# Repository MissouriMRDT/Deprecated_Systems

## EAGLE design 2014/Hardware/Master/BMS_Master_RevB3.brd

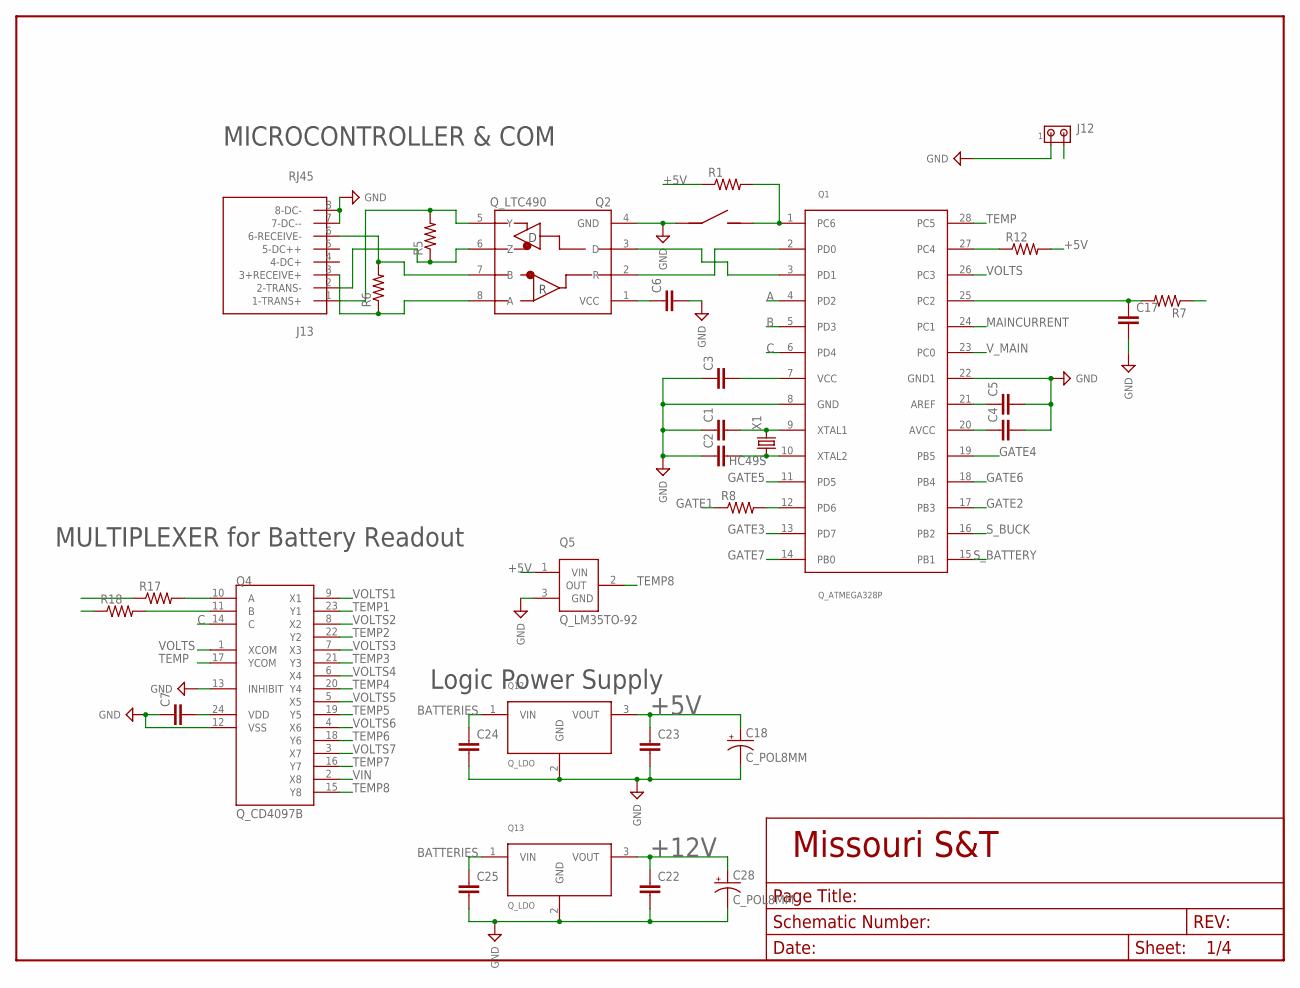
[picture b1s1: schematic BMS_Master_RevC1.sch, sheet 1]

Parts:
C1, C2, C3, C4, C5, C6, C7, C17, C22, C23, C24, C25: C_CAP_1206; C_1206
C18, C28: C_POL8MM; C_8MM
J1: J_MC32857; J_TOGGLE
J12: J_MTA2P_100; J_MTA100_2P
J13: RJ45; RJ45-CAT5E
Q1: Q_ATMEGA328P; DIP28
Q2: Q_LTC490; DIP8
Q4: Q_CD4097B; WDIP24
Q5: Q_LM35TO-92; TO-92-3
Q12, Q13: Q_LDO; TO-220
R1, R5, R6: R_RES_1206; R_1206
R7, R8, R17, R18: R_1/4W
R12: R_RES_0805; R_0805
X1: HC49S; HC-49

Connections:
+5V: C3.2, C4.1, C6.1, C7.2, C18.+, C23.1, Q1.7 (VCC), Q1.20 (AVCC), Q2.1 (VCC), Q4.24 (VDD), Q5.1 (VIN), Q12.3 (VOUT), R1.1, R12.2; also elsewhere on the board
+12V: C22.1, C28.+, Q13.3 (VOUT); also elsewhere on the board
A: Q1.4 (PD2), R17.1
B: Q1.5 (PD3), R18.1
BATTERIES: C24.1, C25.1, Q12.1 (VIN), Q13.1 (VIN); also elsewhere on the board
C: Q1.6 (PD4), Q4.14 (C)
CURRENT: R7.1; also elsewhere on the board
GATE1: R8.1; also elsewhere on the board
GATE2: Q1.17 (PB3); also elsewhere on the board
GATE3: Q1.13 (PD7); also elsewhere on the board
GATE4: Q1.19 (PB5); also elsewhere on the board
GATE5: Q1.11 (PD5); also elsewhere on the board
GATE6: Q1.18 (PB4); also elsewhere on the board
GATE7: Q1.14 (PB0); also elsewhere on the board
GND: C1.1, C2.1, C3.1, C4.2, C5.2, C6.2, C7.1, C17.2, C18.-, C22.2, C23.2, C24.2, C25.2, C28.-, J1.P$1 (1), J12.1, J13.7 (7-DC--), J13.8 (8-DC-), Q1.8 (GND), Q1.22 (GND1), Q2.4 (GND), Q4.12 (VSS), Q4.13 (INHIBIT), Q5.3 (GND), Q12.2 (GND), Q13.2 (GND); also elsewhere on the board
MAINCURRENT: Q1.24 (PC1); also elsewhere on the board
unnamed: C2.2, Q1.10 (XTAL2), X1.P$1 (1)
unnamed: C1.2, Q1.9 (XTAL1), X1.P$2 (2)
unnamed: Q4.10 (A), R17.2
unnamed: C5.1, Q1.21 (AREF)
unnamed: Q4.11 (B), R18.2
unnamed: J1.P$2 (2), Q1.1 (PC6), R1.2
unnamed: C17.1, Q1.25 (PC2), R7.2
unnamed: Q1.12 (PD6), R8.2
unnamed: Q1.2 (PD0), Q2.2 (R)
unnamed: Q1.3 (PD1), Q2.3 (D)
unnamed: J13.1 (1-TRANS+), Q2.5 (Y), R5.2
unnamed: J13.2 (2-TRANS-), Q2.6 (Z), R5.1
unnamed: J13.6 (6-RECEIVE-), Q2.7 (B), R6.2
unnamed: J13.3 (3+RECEIVE+), Q2.8 (A), R6.1
PANIC: J12.2, Q1.27 (PC4), R12.1
S_BATTERY: Q1.15 (PB1); also elsewhere on the board
S_BUCK: Q1.16 (PB2); also elsewhere on the board
TEMP: Q1.28 (PC5), Q4.17 (YCOM)
TEMP1: Q4.23 (Y1); also elsewhere on the board
TEMP2: Q4.22 (Y2); also elsewhere on the board
TEMP3: Q4.21 (Y3); also elsewhere on the board
TEMP4: Q4.20 (Y4); also elsewhere on the board
TEMP5: Q4.19 (Y5); also elsewhere on the board
TEMP6: Q4.18 (Y6); also elsewhere on the board
TEMP7: Q4.16 (Y7); also elsewhere on the board
TEMP8: Q4.15 (Y8), Q5.2 (OUT)
VIN: Q4.2 (X8); also elsewhere on the board
VOLTS: Q1.26 (PC3), Q4.1 (XCOM)
VOLTS1: Q4.9 (X1); also elsewhere on the board
VOLTS2: Q4.8 (X2); also elsewhere on the board
VOLTS3: Q4.7 (X3); also elsewhere on the board
VOLTS4: Q4.6 (X4); also elsewhere on the board
VOLTS5: Q4.5 (X5); also elsewhere on the board
VOLTS6: Q4.4 (X6); also elsewhere on the board
VOLTS7: Q4.3 (X7); also elsewhere on the board
V_MAIN: Q1.23 (PC0); also elsewhere on the board

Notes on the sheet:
MICROCONTROLLER & COM
MULTIPLEXER for Battery Readout
Logic Power Supply

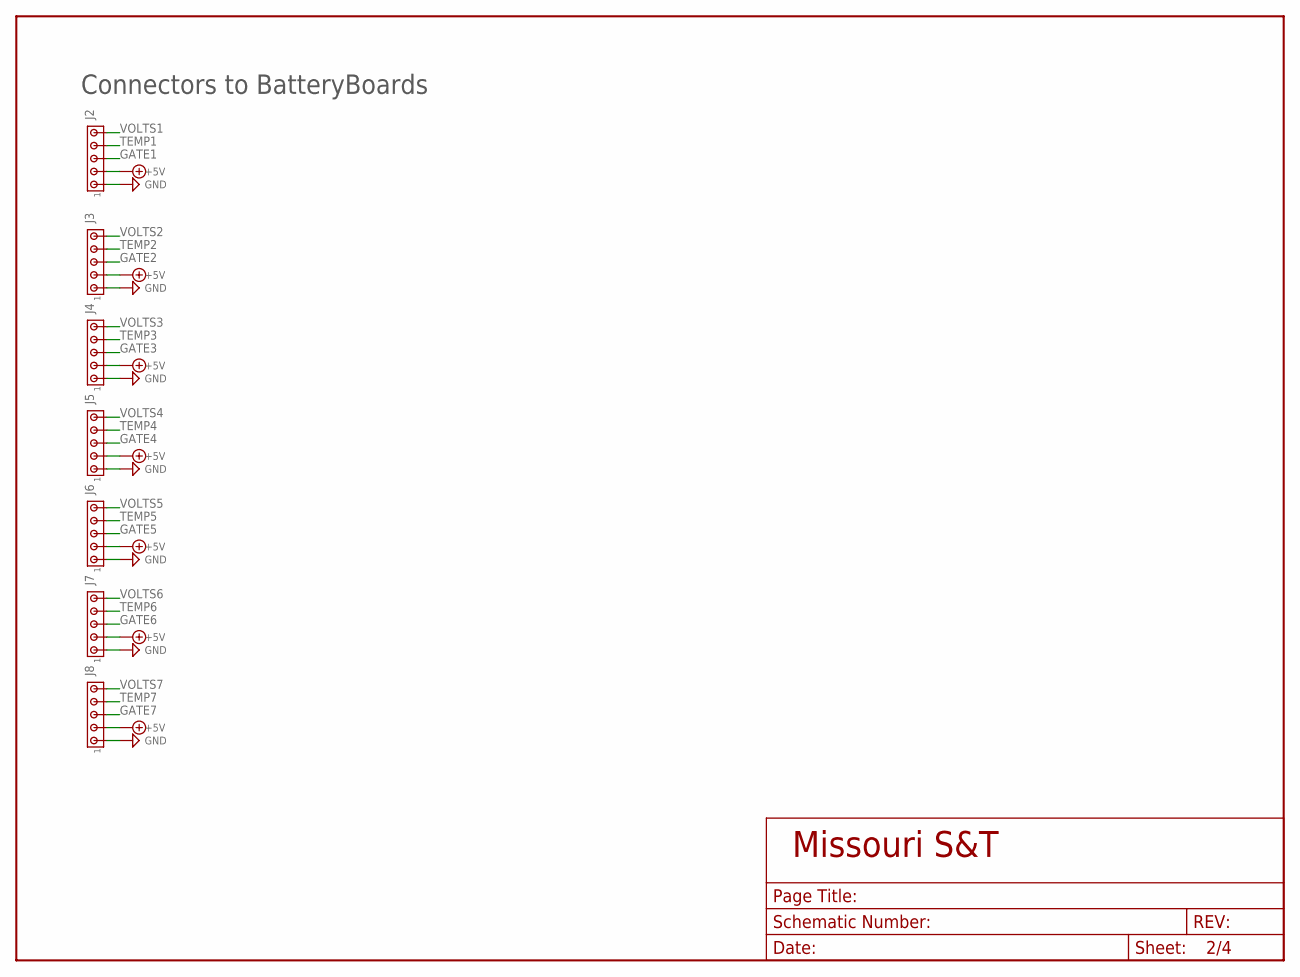
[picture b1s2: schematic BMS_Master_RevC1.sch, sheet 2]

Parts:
J2, J3, J4, J5, J6, J7, J8: J_MTA5P_100; J_MTA100_5P

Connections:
+5V: J2.2, J3.2, J4.2, J5.2, J6.2, J7.2, J8.2; also elsewhere on the board
GATE1: J2.3; also elsewhere on the board
GATE2: J3.3; also elsewhere on the board
GATE3: J4.3; also elsewhere on the board
GATE4: J5.3; also elsewhere on the board
GATE5: J6.3; also elsewhere on the board
GATE6: J7.3; also elsewhere on the board
GATE7: J8.3; also elsewhere on the board
GND: J2.1, J3.1, J4.1, J5.1, J6.1, J7.1, J8.1; also elsewhere on the board
TEMP1: J2.4; also elsewhere on the board
TEMP2: J3.4; also elsewhere on the board
TEMP3: J4.4; also elsewhere on the board
TEMP4: J5.4; also elsewhere on the board
TEMP5: J6.4; also elsewhere on the board
TEMP6: J7.4; also elsewhere on the board
TEMP7: J8.4; also elsewhere on the board
VOLTS1: J2.5; also elsewhere on the board
VOLTS2: J3.5; also elsewhere on the board
VOLTS3: J4.5; also elsewhere on the board
VOLTS4: J5.5; also elsewhere on the board
VOLTS5: J6.5; also elsewhere on the board
VOLTS6: J7.5; also elsewhere on the board
VOLTS7: J8.5; also elsewhere on the board

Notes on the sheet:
Connectors to BatteryBoards

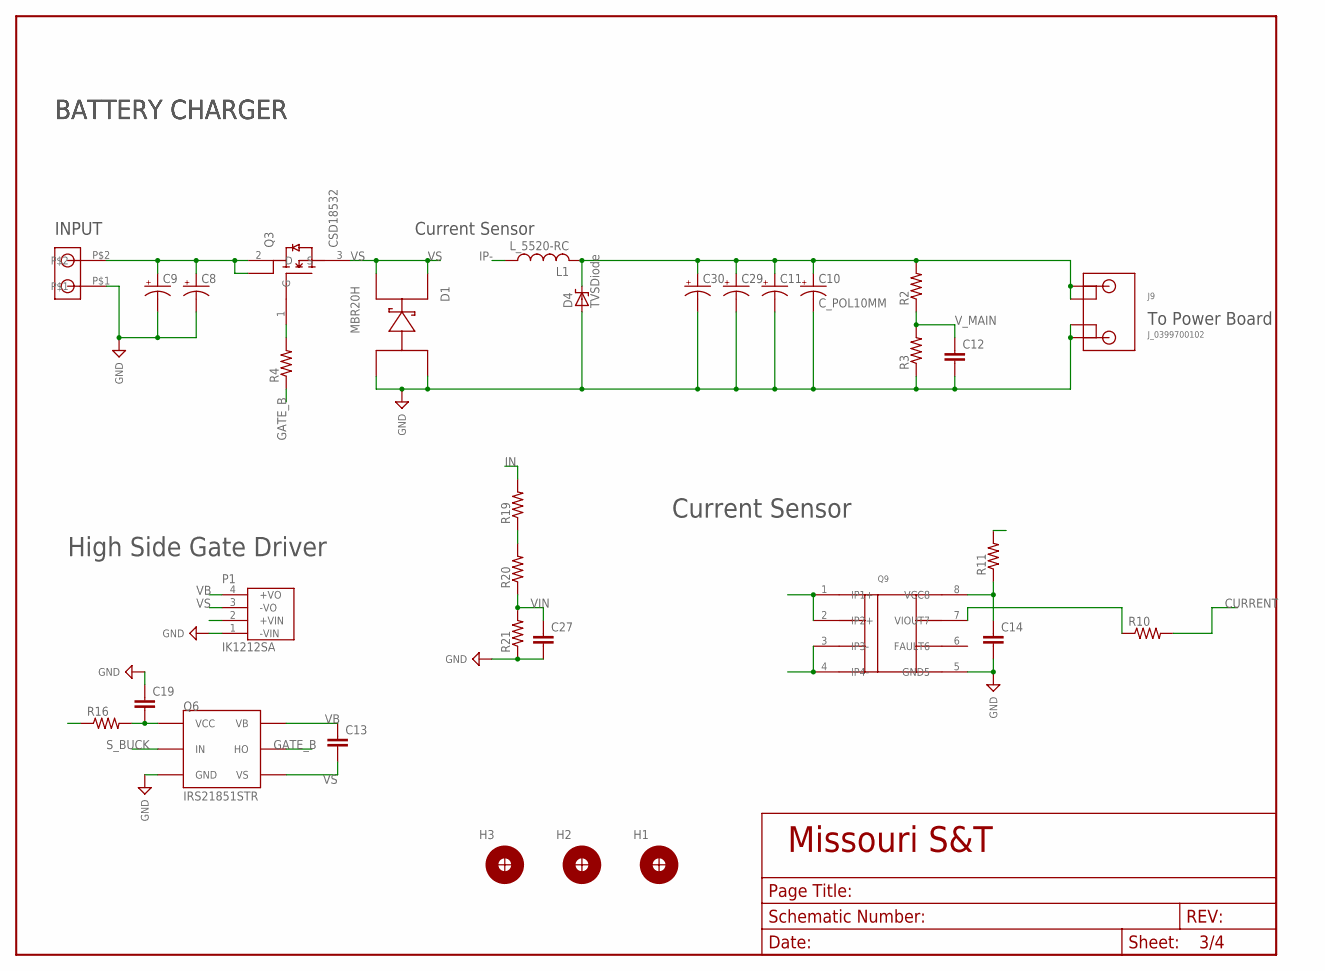
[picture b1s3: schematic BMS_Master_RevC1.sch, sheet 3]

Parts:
C8, C9, C10, C11, C29, C30: C_POL10MM; C_10MM
C12, C13, C14, C19, C27: C_CAP_1206; C_1206
D1: MBR20H; TO-220-FLAT
D4: TVSDiode; DIODE_D3.5MM_LS15.24MM
H1, H2, H3: H_MNTHOLE_#6
J9: J_0399700102; J_2CONHC
J10: J_1546074-2; THERM_BLOCK_2
L1: L_5520-RC
P1: IK1212SA; TME1215S
Q3: CSD18532; TO-220-FLAT
Q6: IRS21851STR; SOIC8
Q9: Q_SO8ACS711; Q_SO8
R2, R10, R11, R16, R19, R20: R_1/4W
R3, R4, R21: R_RES_1206; R_1206

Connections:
+5V: R11.2; also elsewhere on the board
+5V1: C14.1, Q9.8 (VCC8), R11.1; also elsewhere on the board
+12V: R16.1; also elsewhere on the board
+12V1: C19.2, P1.2 (+VIN), Q6.1 (VCC), R16.2
CURRENT: R10.2; also elsewhere on the board
GATE_B: Q6.7 (HO), R4.1
GND: C8.P$2 (-), C9.P$2 (-), C10.P$2 (-), C11.P$2 (-), C12.2, C14.2, C19.1, C27.2, C29.P$2 (-), C30.P$2 (-), D1.1 (A1), D1.3 (A2), D4.A, J9.PIN2-1 (2-1), J9.PIN2-2 (2-2), J10.P$1, P1.1 (-VIN), Q6.4 (GND), Q9.5 (GND5), R3.1, R21.1; also elsewhere on the board
IN: C8.P$1 (+), C9.P$1 (+), J10.P$2, Q3.2 (D), Q3.4, R19.2
IP-: L1.1, Q9.1 (IP1+), Q9.2 (IP2+)
MAIN: C10.P$1 (+), C11.P$1 (+), C29.P$1 (+), C30.P$1 (+), D4.C (K), J9.PIN1-1 (1-1), J9.PIN1-2 (1-2), L1.2, R2.2; also elsewhere on the board
unnamed: Q9.7 (VIOUT7), R10.1
unnamed: R19.1, R20.2
unnamed: Q3.1 (G), R4.2
S_BUCK: Q6.2 (IN); also elsewhere on the board
VB: C13.1, P1.4 (+VO), Q6.8 (VB)
VIN: C27.1, R20.1, R21.2; also elsewhere on the board
VS: C13.2, D1.2 (C1), D1.4 (C2), P1.3 (-VO), Q3.3 (S), Q6.6 (VS), Q9.3 (IP3-), Q9.4 (IP4-)
V_MAIN: C12.1, R2.1, R3.2; also elsewhere on the board

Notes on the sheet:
BATTERY CHARGER
INPUT
Current Sensor
High Side Gate Driver
To Power Board

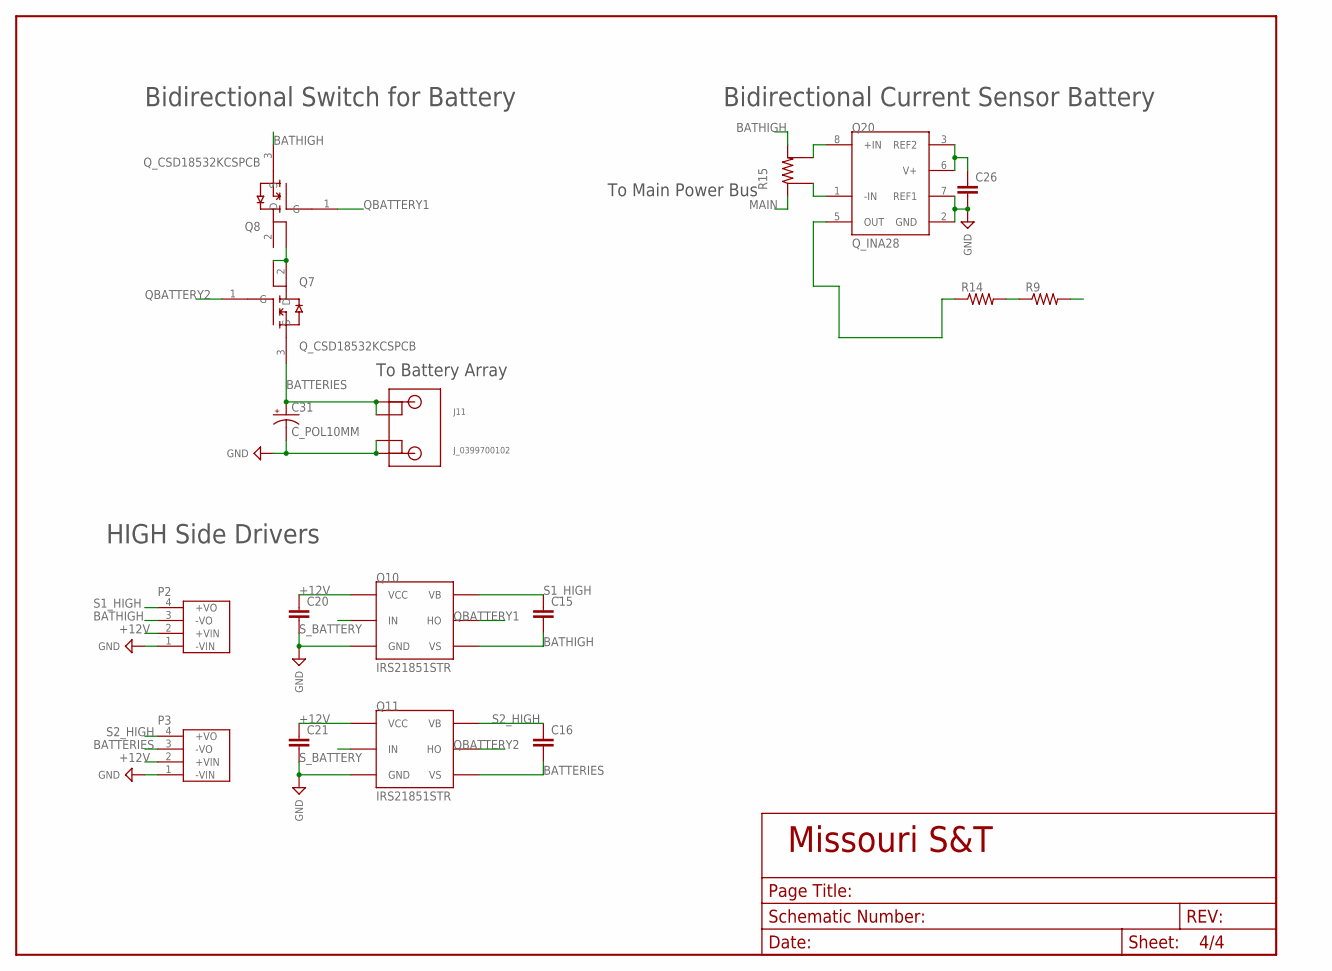
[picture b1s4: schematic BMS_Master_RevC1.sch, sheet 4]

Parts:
C15, C16, C20, C21, C26: C_CAP_1206; C_1206
C31: C_POL10MM; C_10MM
J11: J_0399700102; J_2CONHC
P2, P3: TME1215S
Q7, Q8: Q_CSD18532KCSPCB; TO-220-FLAT
Q10, Q11: IRS21851STR; SOIC8
Q20: Q_INA28; SOIC8
R9, R14: R_1/4W
R15: R_FC4L110R001JER; R_FC4L

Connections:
+5V1: C26.1, Q20.3 (REF2), Q20.6 (V+); also elsewhere on the board
+12V: C20.1, C21.1, P2.2 (+VIN), P3.2 (+VIN), Q10.1 (VCC), Q11.1 (VCC); also elsewhere on the board
BATHIGH: C15.2, P2.3 (-VO), Q8.3 (S), Q10.6 (VS), R15.2
BATTERIES: C16.2, C31.P$1 (+), J11.PIN1-1 (1-1), J11.PIN1-2 (1-2), P3.3 (-VO), Q7.3 (S), Q11.6 (VS); also elsewhere on the board
GND: C20.2, C21.2, C26.2, C31.P$2 (-), J11.PIN2-1 (2-1), J11.PIN2-2 (2-2), P2.1 (-VIN), P3.1 (-VIN), Q10.4 (GND), Q11.4 (GND), Q20.2 (GND), Q20.7 (REF1); also elsewhere on the board
INT_BAT: Q7.2 (D), Q7.4, Q8.4
MAIN: R15.1; also elsewhere on the board
MAINCURRENT: R9.2; also elsewhere on the board
unnamed: Q20.5 (OUT), R14.1
unnamed: Q20.8 (+IN), R15.SENSE2
unnamed: Q20.1 (-IN), R15.SENSE1
unnamed: R9.1, R14.2
QBATTERY1: Q8.1 (G), Q10.7 (HO)
QBATTERY2: Q7.1 (G), Q11.7 (HO)
S1_HIGH: C15.1, P2.4 (+VO), Q10.8 (VB)
S2_HIGH: C16.1, P3.4 (+VO), Q11.8 (VB)
S_BATTERY: Q10.2 (IN), Q11.2 (IN); also elsewhere on the board

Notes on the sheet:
HIGH Side Drivers
Bidirectional Switch for Battery
Bidirectional Current Sensor Battery
To Battery Array
To Main Power Bus

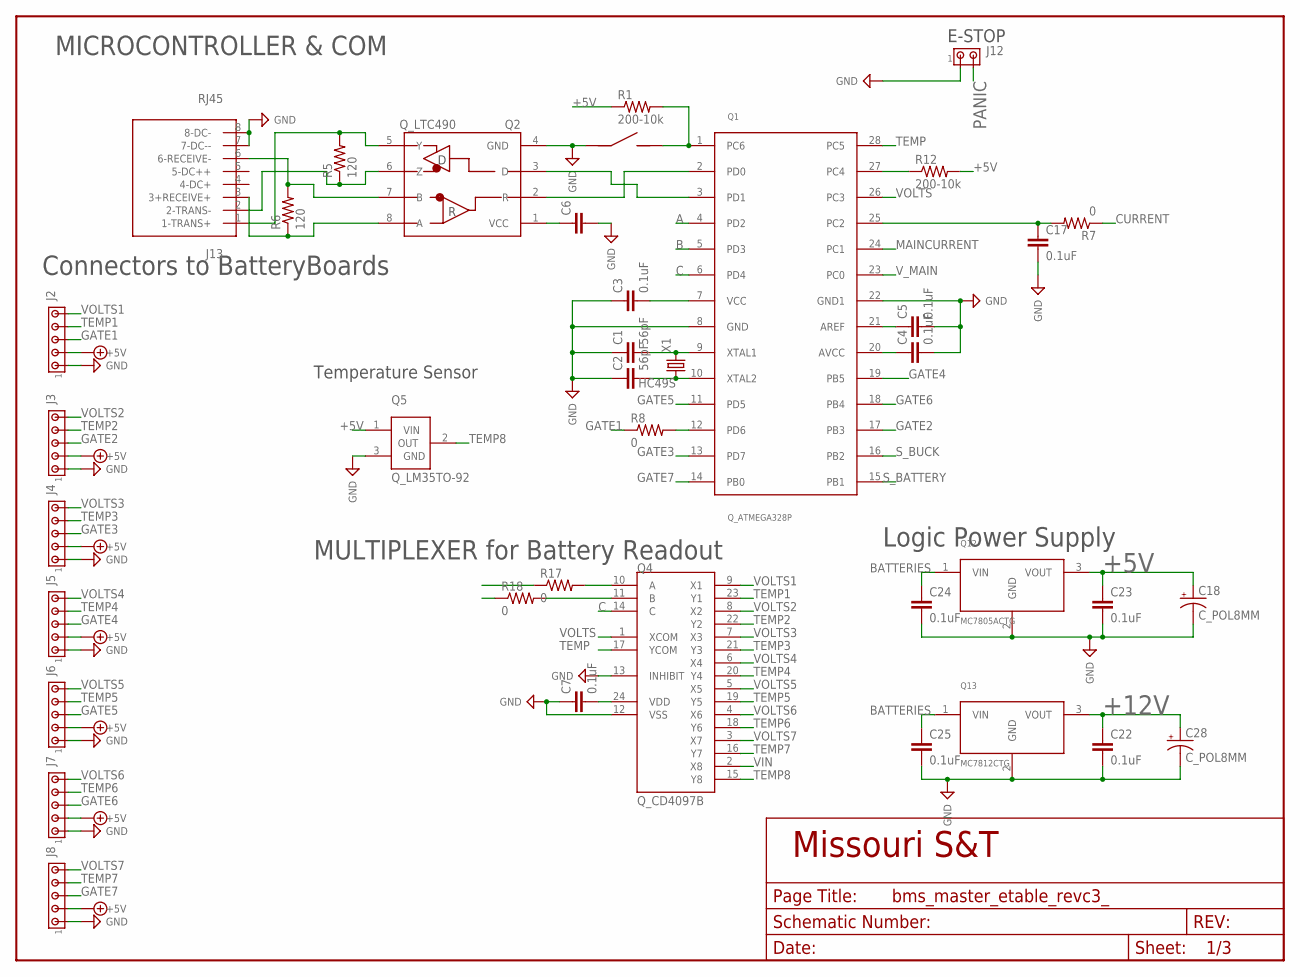
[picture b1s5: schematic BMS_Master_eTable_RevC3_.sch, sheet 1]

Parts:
C1, C2: 56pF; C_1206
C3, C4, C5, C7, C17, C22, C23, C24, C25: 0.1uF; C_1206
C6: C_CAP_1206; C_1206
C18, C28: C_POL8MM; C_8MM
J1: J_MC32857; J_TOGGLE
J2, J3, J4, J5, J6, J7, J8: J_MTA5P_100; J_MTA100_5P
J12: J_MTA2P_100; J_MTA100_2P
J13: RJ45; RJ45-CAT5E
Q1: Q_ATMEGA328P; DIP28
Q2: Q_LTC490; DIP8
Q4: Q_CD4097B; WDIP24
Q5: Q_LM35TO-92; TO-92-3
Q12: MC7805ACTG; TO-220
Q13: MC7812CTG; TO-220
R1: 200-10k; R_1206
R5, R6: 120; R_1206
R7, R8, R17, R18: 0; R_1/4W
R12: 200-10k; R_0805
X1: HC49S; HC-49

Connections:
+5V: C3.2, C4.1, C6.1, C7.2, C18.+, C23.1, J2.2, J3.2, J4.2, J5.2, J6.2, J7.2, J8.2, Q1.7 (VCC), Q1.20 (AVCC), Q2.1 (VCC), Q4.24 (VDD), Q5.1 (VIN), Q12.3 (VOUT), R1.1, R12.2; also elsewhere on the board
+12V: C22.1, C28.+, Q13.3 (VOUT); also elsewhere on the board
A: Q1.4 (PD2), R17.1
B: Q1.5 (PD3), R18.1
BATTERIES: C24.1, C25.1, Q12.1 (VIN), Q13.1 (VIN); also elsewhere on the board
C: Q1.6 (PD4), Q4.14 (C)
CURRENT: R7.1; also elsewhere on the board
GATE1: J2.3, R8.1
GATE2: J3.3, Q1.17 (PB3)
GATE3: J4.3, Q1.13 (PD7)
GATE4: J5.3, Q1.19 (PB5)
GATE5: J6.3, Q1.11 (PD5)
GATE6: J7.3, Q1.18 (PB4)
GATE7: J8.3, Q1.14 (PB0)
GND: C1.1, C2.1, C3.1, C4.2, C5.2, C6.2, C7.1, C17.2, C18.-, C22.2, C23.2, C24.2, C25.2, C28.-, J1.P$1 (1), J2.1, J3.1, J4.1, J5.1, J6.1, J7.1, J8.1, J12.1, J13.7 (7-DC--), J13.8 (8-DC-), Q1.8 (GND), Q1.22 (GND1), Q2.4 (GND), Q4.12 (VSS), Q4.13 (INHIBIT), Q5.3 (GND), Q12.2 (GND), Q13.2 (GND); also elsewhere on the board
MAINCURRENT: Q1.24 (PC1); also elsewhere on the board
unnamed: C2.2, Q1.10 (XTAL2), X1.P$1 (1)
unnamed: C1.2, Q1.9 (XTAL1), X1.P$2 (2)
unnamed: Q4.10 (A), R17.2
unnamed: C5.1, Q1.21 (AREF)
unnamed: Q4.11 (B), R18.2
unnamed: J1.P$2 (2), Q1.1 (PC6), R1.2
unnamed: C17.1, Q1.25 (PC2), R7.2
unnamed: Q1.12 (PD6), R8.2
unnamed: Q1.2 (PD0), Q2.2 (R)
unnamed: Q1.3 (PD1), Q2.3 (D)
unnamed: J13.1 (1-TRANS+), Q2.5 (Y), R5.2
unnamed: J13.2 (2-TRANS-), Q2.6 (Z), R5.1
unnamed: J13.6 (6-RECEIVE-), Q2.7 (B), R6.2
unnamed: J13.3 (3+RECEIVE+), Q2.8 (A), R6.1
PANIC: J12.2, Q1.27 (PC4), R12.1
S_BATTERY: Q1.15 (PB1); also elsewhere on the board
S_BUCK: Q1.16 (PB2); also elsewhere on the board
TEMP: Q1.28 (PC5), Q4.17 (YCOM)
TEMP1: J2.4, Q4.23 (Y1)
TEMP2: J3.4, Q4.22 (Y2)
TEMP3: J4.4, Q4.21 (Y3)
TEMP4: J5.4, Q4.20 (Y4)
TEMP5: J6.4, Q4.19 (Y5)
TEMP6: J7.4, Q4.18 (Y6)
TEMP7: J8.4, Q4.16 (Y7)
TEMP8: Q4.15 (Y8), Q5.2 (OUT)
VIN: Q4.2 (X8); also elsewhere on the board
VOLTS: Q1.26 (PC3), Q4.1 (XCOM)
VOLTS1: J2.5, Q4.9 (X1)
VOLTS2: J3.5, Q4.8 (X2)
VOLTS3: J4.5, Q4.7 (X3)
VOLTS4: J5.5, Q4.6 (X4)
VOLTS5: J6.5, Q4.5 (X5)
VOLTS6: J7.5, Q4.4 (X6)
VOLTS7: J8.5, Q4.3 (X7)
V_MAIN: Q1.23 (PC0); also elsewhere on the board

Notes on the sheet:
MICROCONTROLLER & COM
MULTIPLEXER for Battery Readout
Logic Power Supply
Connectors to BatteryBoards
Temperature Sensor
E-STOP

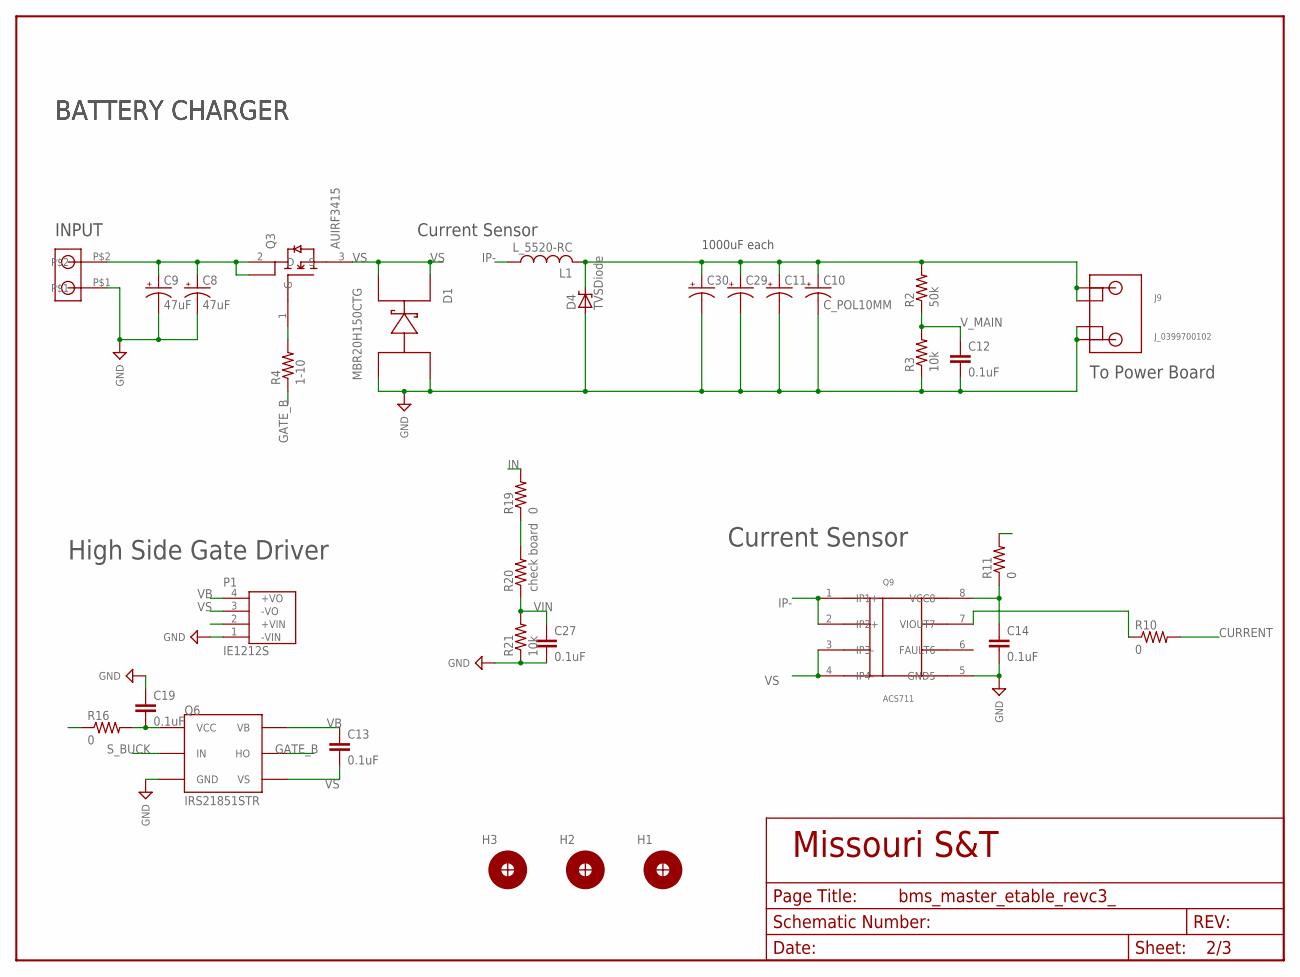
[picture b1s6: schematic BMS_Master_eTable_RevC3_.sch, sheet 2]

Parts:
C8, C9: 47uF; C_10MM
C10, C11, C29, C30: C_POL10MM; C_10MM
C12, C13, C14, C19, C27: 0.1uF; C_1206
D1: MBR20H150CTG; TO-220-FLAT
D4: TVSDiode; DIODE_D3.5MM_LS15.24MM
H1, H2, H3: H_MNTHOLE_#6
J9: J_0399700102; J_2CONHC
J10: J_1546074-2; THERM_BLOCK_2
L1: L_5520-RC
P1: IE1212S; TME1215S
Q3: AUIRF3415; TO-220-FLAT
Q6: IRS21851STR; SOIC8
Q9: ACS711; Q_SO8
R2: 50k; R_1/4W
R3, R21: 10k; R_1206
R4: 1-10; R_1206
R10, R11, R16, R19: 0; R_1/4W
R20: check board; R_1/4W

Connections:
+5V: R11.2; also elsewhere on the board
+5V1: C14.1, Q9.8 (VCC8), R11.1; also elsewhere on the board
+12V: R16.1; also elsewhere on the board
+12V1: C19.2, P1.2 (+VIN), Q6.1 (VCC), R16.2
CURRENT: R10.2; also elsewhere on the board
GATE_B: Q6.7 (HO), R4.1
GND: C8.P$2 (-), C9.P$2 (-), C10.P$2 (-), C11.P$2 (-), C12.2, C14.2, C19.1, C27.2, C29.P$2 (-), C30.P$2 (-), D1.1 (A1), D1.3 (A2), D4.A, J9.PIN2-1 (2-1), J9.PIN2-2 (2-2), J10.P$1, P1.1 (-VIN), Q6.4 (GND), Q9.5 (GND5), R3.1, R21.1; also elsewhere on the board
IN: C8.P$1 (+), C9.P$1 (+), J10.P$2, Q3.2 (D), Q3.4, R19.2
IP-: L1.1, Q9.1 (IP1+), Q9.2 (IP2+)
MAIN: C10.P$1 (+), C11.P$1 (+), C29.P$1 (+), C30.P$1 (+), D4.C (K), J9.PIN1-1 (1-1), J9.PIN1-2 (1-2), L1.2, R2.2; also elsewhere on the board
unnamed: Q9.7 (VIOUT7), R10.1
unnamed: R19.1, R20.2
unnamed: Q3.1 (G), R4.2
S_BUCK: Q6.2 (IN); also elsewhere on the board
VB: C13.1, P1.4 (+VO), Q6.8 (VB)
VIN: C27.1, R20.1, R21.2; also elsewhere on the board
VS: C13.2, D1.2 (C1), D1.4 (C2), P1.3 (-VO), Q3.3 (S), Q6.6 (VS), Q9.3 (IP3-), Q9.4 (IP4-)
V_MAIN: C12.1, R2.1, R3.2; also elsewhere on the board

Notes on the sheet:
BATTERY CHARGER
INPUT
Current Sensor
High Side Gate Driver
To Power Board
1000uF each

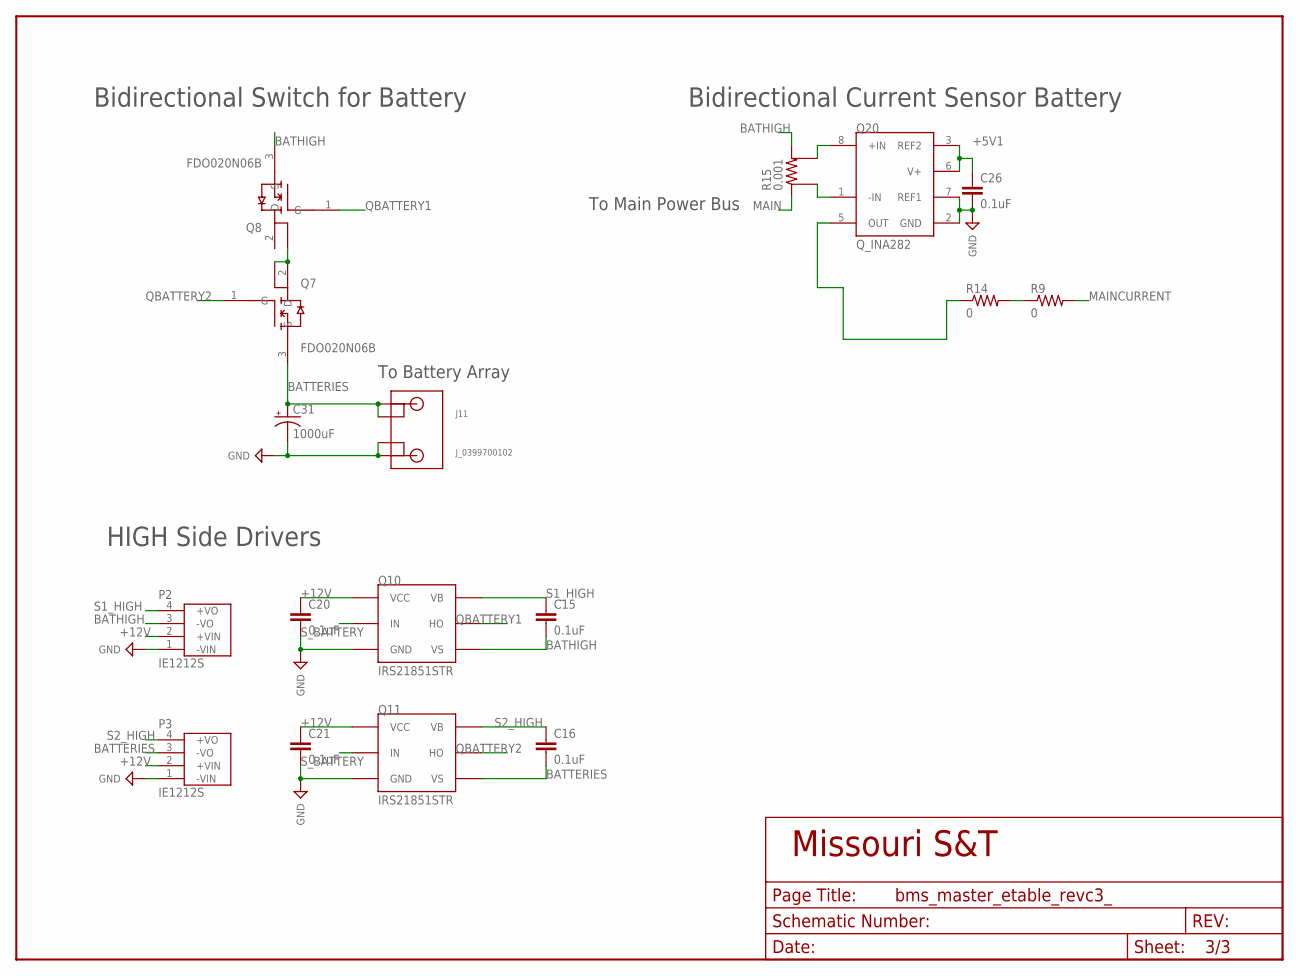
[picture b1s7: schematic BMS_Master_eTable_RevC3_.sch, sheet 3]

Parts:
C15, C16, C20, C21, C26: 0.1uF; C_1206
C31: 1000uF; C_10MM
J11: J_0399700102; J_2CONHC
P2, P3: IE1212S; TME1215S
Q7, Q8: FDO020N06B; TO-220-FLAT
Q10, Q11: IRS21851STR; SOIC8
Q20: Q_INA282; SOIC8
R9, R14: 0; R_1/4W
R15: 0.001; R_FC4L

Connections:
+5V1: C26.1, Q20.3 (REF2), Q20.6 (V+); also elsewhere on the board
+12V: C20.1, C21.1, P2.2 (+VIN), P3.2 (+VIN), Q10.1 (VCC), Q11.1 (VCC); also elsewhere on the board
BATHIGH: C15.2, P2.3 (-VO), Q8.3 (S), Q10.6 (VS), R15.2
BATTERIES: C16.2, C31.P$1 (+), J11.PIN1-1 (1-1), J11.PIN1-2 (1-2), P3.3 (-VO), Q7.3 (S), Q11.6 (VS); also elsewhere on the board
GND: C20.2, C21.2, C26.2, C31.P$2 (-), J11.PIN2-1 (2-1), J11.PIN2-2 (2-2), P2.1 (-VIN), P3.1 (-VIN), Q10.4 (GND), Q11.4 (GND), Q20.2 (GND), Q20.7 (REF1); also elsewhere on the board
INT_BAT: Q7.2 (D), Q7.4, Q8.4
MAIN: R15.1; also elsewhere on the board
MAINCURRENT: R9.2; also elsewhere on the board
unnamed: Q20.5 (OUT), R14.1
unnamed: Q20.8 (+IN), R15.SENSE2
unnamed: Q20.1 (-IN), R15.SENSE1
unnamed: R9.1, R14.2
QBATTERY1: Q8.1 (G), Q10.7 (HO)
QBATTERY2: Q7.1 (G), Q11.7 (HO)
S1_HIGH: C15.1, P2.4 (+VO), Q10.8 (VB)
S2_HIGH: C16.1, P3.4 (+VO), Q11.8 (VB)
S_BATTERY: Q10.2 (IN), Q11.2 (IN); also elsewhere on the board

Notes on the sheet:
HIGH Side Drivers
Bidirectional Switch for Battery
Bidirectional Current Sensor Battery
To Battery Array
To Main Power Bus

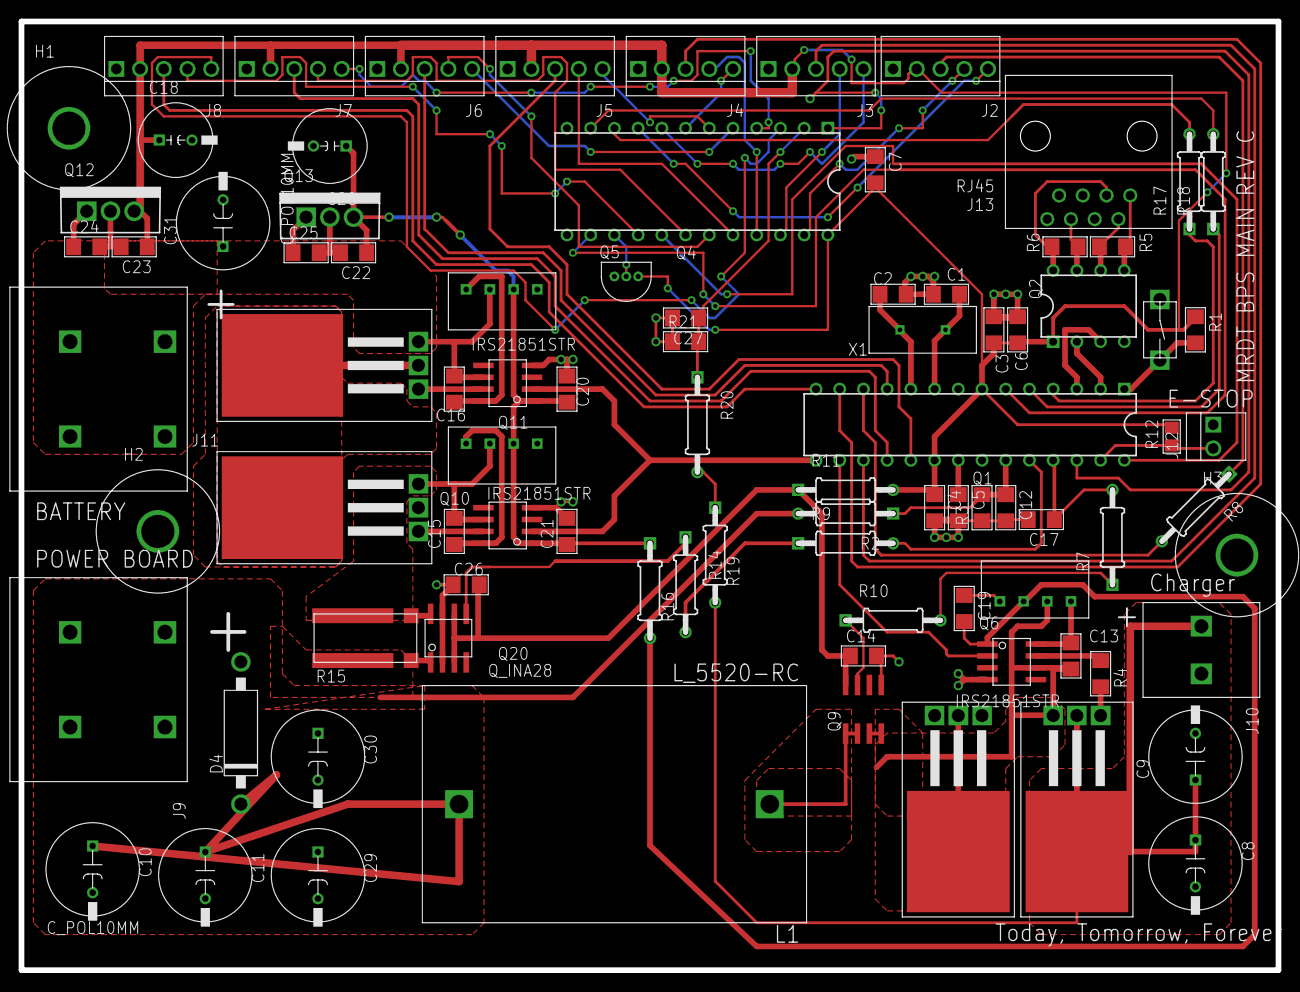
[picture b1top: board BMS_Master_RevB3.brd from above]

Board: 2 copper layers, 134.6 x 101.6 mm, 88 parts (0 on the bottom side), 73 nets.

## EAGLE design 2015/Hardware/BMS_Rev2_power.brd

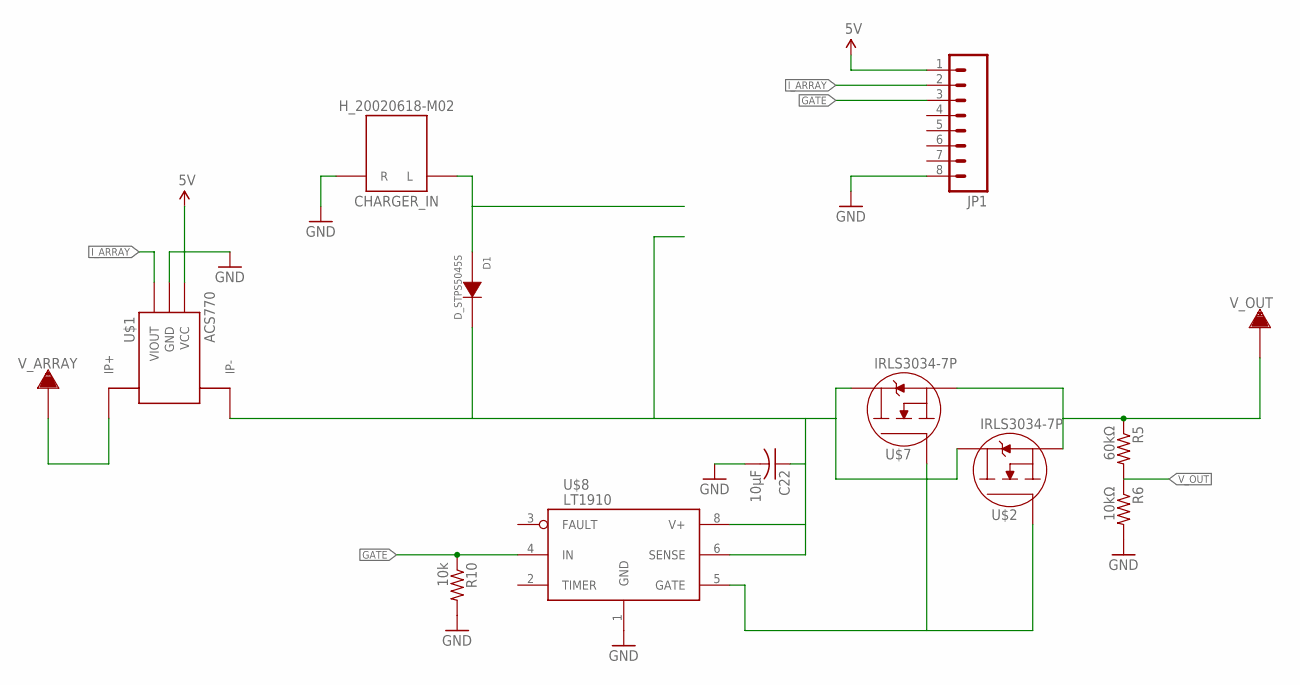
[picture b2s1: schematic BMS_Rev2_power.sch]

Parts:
C22: 10µF; C1206
CHARGER_IN: H_20020618-M02; 20020618-M02
D1: D_STPS5045S; D2PACK
JP1: M08BM08B-SRSS-TB; BM08B-SRSS-TB
R5: 60kΩ; R1206
R6: 10kΩ; R1206
R10: 10k; R1206
U$1: ACS770; PFF_LEADFORM
U$2, U$7: IRLS3034-7P; D2PAK-7
U$8: LT1910; SO8
V_ARRAY: TERMINAL_HOLE; LARGE_TERMINAL_HOLE
V_OUT: TERMINAL_HOLE; LARGE_TERMINAL_HOLE

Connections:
5V: JP1.1, U$1.1 (VCC)
GATE: JP1.3, R10.1, U$8.4 (IN)
GND: C22.2, CHARGER_IN.R1 (R), CHARGER_IN.R2 (R), JP1.8, R6.2, R10.2, U$1.2 (GND), U$8.1 (GND)
I_ARRAY: JP1.2, U$1.3 (VIOUT)
unnamed: R5.1, U$2.2 (SOURCE), U$2.3 (SOURCE), U$2.4 (SOURCE), U$2.5 (SOURCE), U$2.6 (SOURCE), U$7.2 (SOURCE), U$7.3 (SOURCE), U$7.4 (SOURCE), U$7.5 (SOURCE), U$7.6 (SOURCE), V_OUT.P$1
unnamed: U$1.4_1 (IP+), U$1.4_2 (IP+), U$1.4_3 (IP+), U$1.4_4 (IP+), U$1.4_5 (IP+), U$1.4_6 (IP+), U$1.4_7 (IP+), U$1.4_8 (IP+), U$1.4_9 (IP+), U$1.4_10 (IP+), U$1.4_11 (IP+), U$1.4_12 (IP+), U$1.4_13 (IP+), U$1.4_14 (IP+), U$1.4_15 (IP+), U$1.4_16 (IP+), U$1.4_B (IP+), U$1.4_T (IP+), V_ARRAY.P$1
unnamed: C22.1, D1.TAB (K), U$1.5_1 (IP-), U$1.5_2 (IP-), U$1.5_3 (IP-), U$1.5_4 (IP-), U$1.5_5 (IP-), U$1.5_6 (IP-), U$1.5_7 (IP-), U$1.5_8 (IP-), U$1.5_9 (IP-), U$1.5_10 (IP-), U$1.5_11 (IP-), U$1.5_12 (IP-), U$1.5_13 (IP-), U$1.5_14 (IP-), U$1.5_15 (IP-), U$1.5_16 (IP-), U$1.5_B (IP-), U$1.5_T (IP-), U$2.PAD (DRAIN), U$7.PAD (DRAIN), U$8.6 (SENSE), U$8.8 (V+)
unnamed: U$2.1 (GATE), U$7.1 (GATE), U$8.5 (GATE)
unnamed: CHARGER_IN.L1 (L), CHARGER_IN.L2 (L), D1.1 (A), D1.2 (A)
V_OUT: R5.2, R6.1

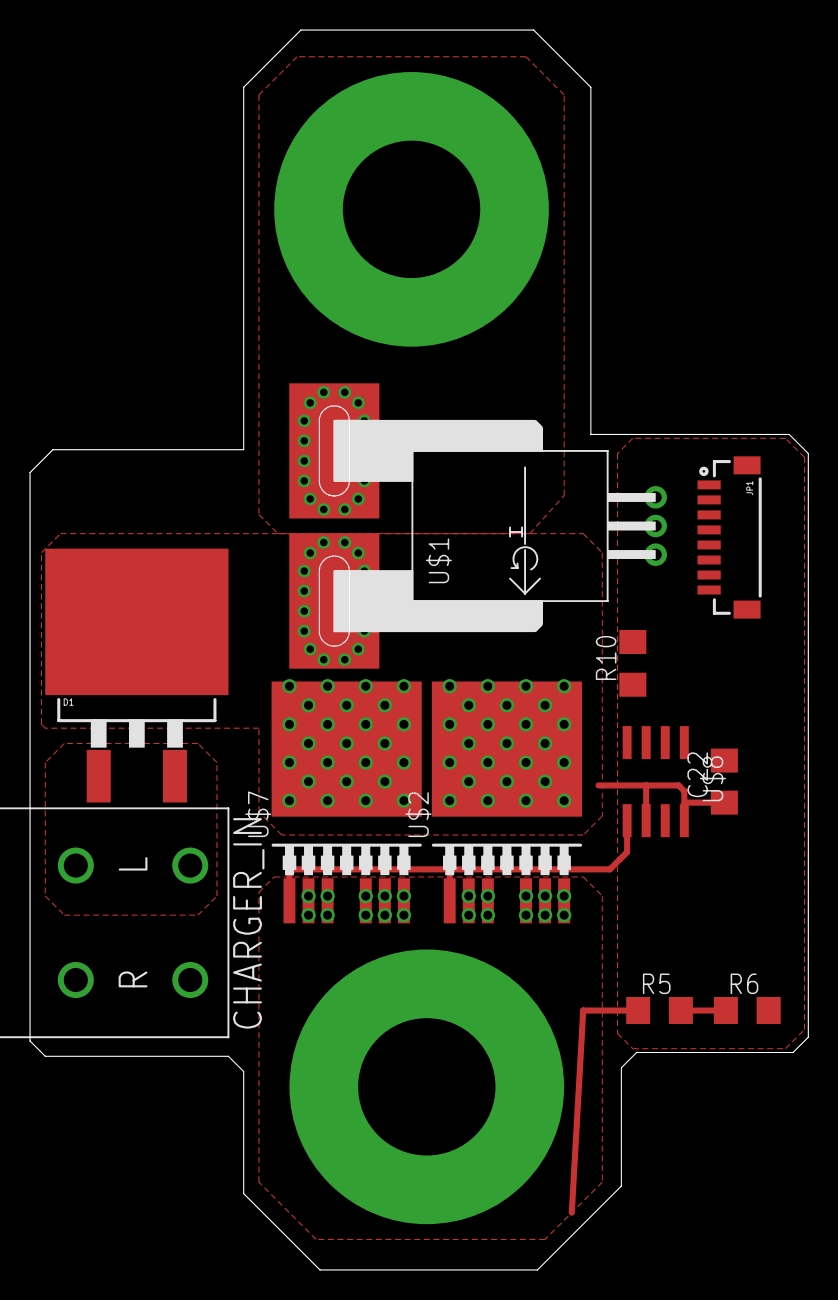
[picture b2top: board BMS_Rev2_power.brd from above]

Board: 2 copper layers, 51.8 x 82.5 mm, 13 parts (0 on the bottom side), 10 nets.

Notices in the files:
parts and their libraries:
SparkFun-Connectors: Licensing: Creative Commons ShareAlike 4.0 International - https://creativecommons.org/licenses/by-sa/4.0
SparkFun-Connectors: Licensing: CC v3.0 Share-Alike You are welcome to use this library for commercial purposes.
